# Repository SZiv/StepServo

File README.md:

# StepServo

Check out the wiki here: http://reprap.org/wiki/StepServo (under construction)

A single channel step/direction/enable/endstop to DC quadrature encoder converter for use with 3D printers or CNC machines. So, basically, a single channel version of my other board, RAMPSSB (https://github.com/SZiv/RAMPSSB), and many of the rules that apply there, apply here. The firmware is identical.

Uses an L298N DC motor driver stacked on standoffs as a driver, and an Arduino Pro Micro as a processor. Designed to need only an arduino Pro Micro, a L298N, some standoffs, an LED, a resistor, a 3mm terminal block, and a bunch of header. Can be assembled easily on your own.

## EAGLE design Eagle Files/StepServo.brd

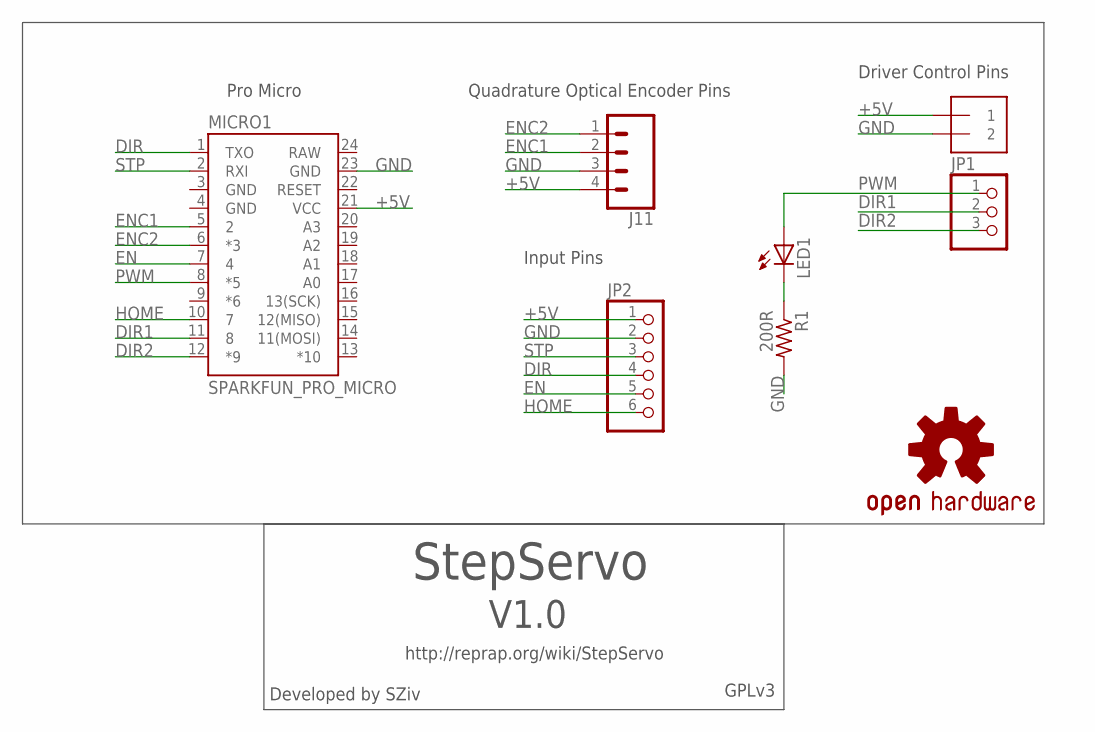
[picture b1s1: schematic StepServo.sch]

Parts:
J2: 1X2-3.5MM
J11: CONN_04; 1X04
JP1: PINHD-1X3; 1X03
JP2: PINHD-1X6; 1X06
LED1: LED3MM
LOGO1: OSHW-LOGOL; OSHW-LOGO-L
MICRO1: SPARKFUN_PRO_MICRO
R1: 200R; 0207/7

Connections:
+5V: J2.1, J11.4, JP2.1, MICRO1.21 (VCC)
DIR: JP2.4, MICRO1.1 (TXO)
DIR1: JP1.2, MICRO1.11 (8)
DIR2: JP1.3, MICRO1.12 (*9)
EN: JP2.5, MICRO1.7 (4)
ENC1: J11.2, MICRO1.5 (2)
ENC2: J11.1, MICRO1.6 (*3)
GND: J2.2, J11.3, JP2.2, MICRO1.3 (GND), MICRO1.4 (GND), MICRO1.23 (GND), R1.2
HOME: JP2.6, MICRO1.10 (7)
unnamed: LED1.K (C), R1.1
PWM: JP1.1, LED1.A, MICRO1.8 (*5)
RAW: MICRO1.24 (RAW)
STP: JP2.3, MICRO1.2 (RXI)

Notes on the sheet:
Quadrature Optical Encoder Pins
StepServo
V1.0
Developed by SZiv
GPLv3
http://reprap.org/wiki/StepServo
Pro Micro
Input Pins
Driver Control Pins

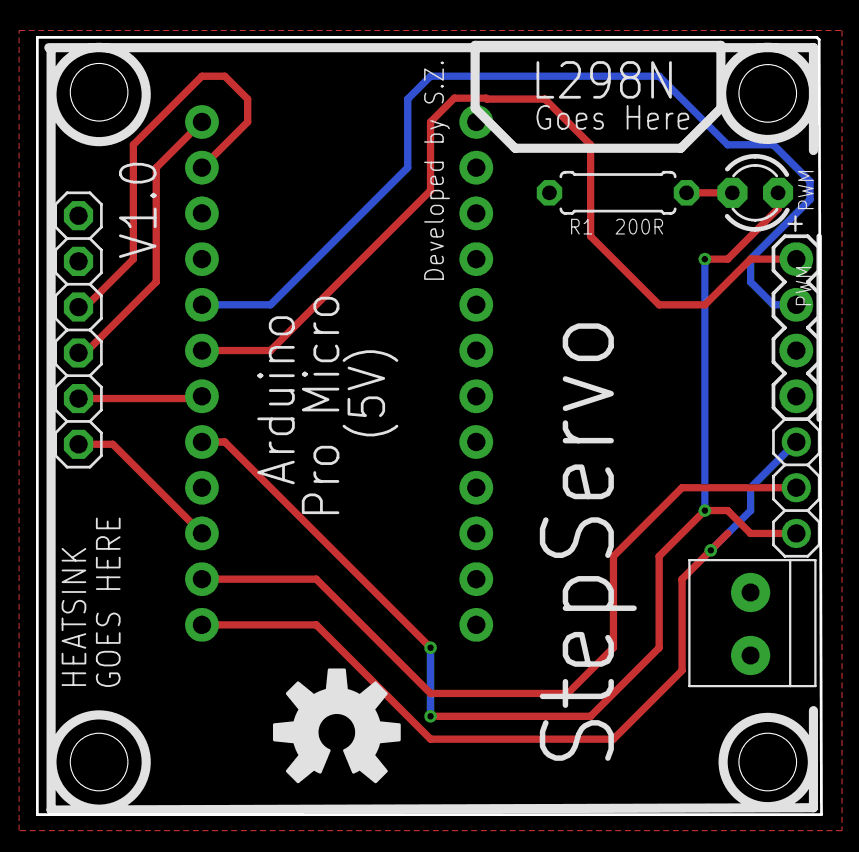
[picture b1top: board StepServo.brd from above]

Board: 2 copper layers, 43.6 x 43.2 mm, 8 parts (0 on the bottom side), 12 nets.

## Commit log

2017-11-19 :neckbeard: Added .gitattributes & .gitignore files
2017-11-19 First Commit!
    First Commit!
2017-11-19 Add Firmware
    Added the Firmware from RAMPSSB
2017-11-19 Fixed some bad markers on silkscreen, and cleaned up schematic
    Fixed some bad markers on silkscreen, and cleaned up schematic

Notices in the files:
parts and their libraries:
SparkFun-Connectors: Licensing: Creative Commons ShareAlike 4.0 International - https://creativecommons.org/licenses/by-sa/4.0
